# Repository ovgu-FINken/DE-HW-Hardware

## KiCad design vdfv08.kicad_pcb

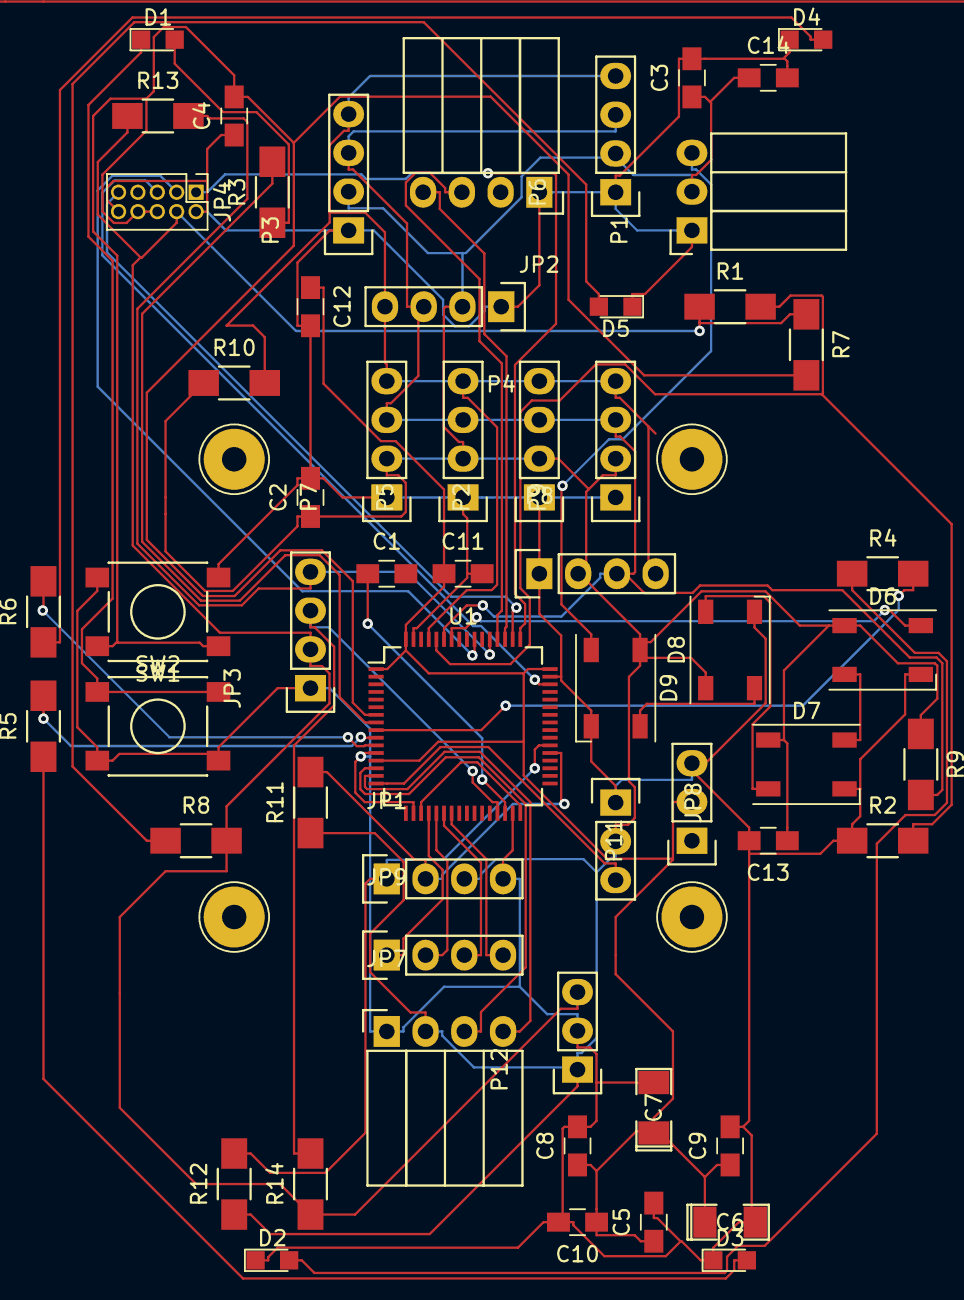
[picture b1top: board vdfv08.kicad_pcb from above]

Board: 2 copper layers, 58 parts (0 on the bottom side), 42 nets.

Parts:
C1: 2.2nF; C_0805_HandSoldering
C2, C3, C8, C9, C10, C11, C12, C13, C14: 0.1U; C_0805_HandSoldering
C4, C5: 10nF; C_0805_HandSoldering
C6: 1U; SMD-1206_Pol
C7: 4.7U; SMD-1206_Pol
D1, D2, D3, D4, D5: LED; LED_0805
D6, D7, D8, D9: WS2812B; LED_WS2812B-PLCC4
JP1: OPTICAL-FLOW; Socket_Strip_Straight_1x04
JP2: AUTOPILOT; Socket_Strip_Angled_1x04
JP3: ILLUMINSENSORI2C2; Socket_Strip_Straight_1x04
JP4: JTAG; Pin_Header_Straight_2x05_Pitch1.27mm
JP7: IR DISTANCE; Socket_Strip_Angled_1x04
JP8: CURENT SENSOR; Socket_Strip_Straight_1x03
JP9: RANGING SENSOR; Socket_Strip_Straight_1x04
P1: CONN WS2812; Socket_Strip_Angled_1x03
P2, P3, P4, P5, P6, P7, P8, P9: I2C-SONAR; Socket_Strip_Straight_1x04
P11: voltage conn; Socket_Strip_Straight_1x03
P12: voltage connector; Socket_Strip_Straight_1x03
R1, R2, R9, R10, R11, R12, R13, R14: 4.7KE; R_1206_HandSoldering
R3, R4, R5, R6, R8: 470E; R_1206_HandSoldering
R7: 10KE; R_1206_HandSoldering
SW1, SW2: SW_PUSH; SW_SPST_PTS645
U1: STM32F446RETx; LQFP-64_10x10mm_Pitch0.5mm

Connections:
/3.3V: JP3.2, JP4.4, P12.3, R1.1, R7.1, R8.2, R13.1, R14.1
/5V: C2.1, C3.1, C13.1, C14.1, D6.1, D7.1, D8.1, D9.1, JP1.3, JP7.2, JP8.2, P1.2, P2.2, P3.2, P4.2, P5.2, P6.2, P7.2, P8.2, P9.2, P12.1, R9.1, R10.1, R11.1, R12.1
/BOOT0: R1.2, R2.2, U1.60
/DIN: D6.4, U1.58
/DIN1: D6.2, D7.4
/DIN2: D7.2, D8.4
/DIN3: D8.2, D9.4
/ENABLE: JP7.4, U1.15
/I2C2SCL: JP3.3, R14.2, U1.29
/I2C2SDA: JP3.4, R13.2, U1.53
/NRST: C4.2, JP4.6, JP4.8, R7.2, SW1.1, U1.7
/OUT: JP7.3, U1.14
/PC0: R3.2, U1.8
/PC1: R4.2, U1.9
/PC2: R5.2, U1.10
/PC3: R6.2, U1.11
/PC10: JP2.4, U1.51
/PC11: JP2.3, U1.52
/SCL: P2.4, P3.4, P4.4, P5.4, P6.4, P7.4, P8.4, P9.4, R10.2, U1.61
/SDA: P2.3, P3.3, P4.3, P5.3, P6.3, P7.3, P8.3, P9.3, R9.2, U1.59
/SDI: JP4.9, U1.50
/SWCLK: JP4.1, U1.49
/SWDIO: JP4.5, U1.46
/SWO: JP4.3, U1.55
GND: C2.2, C3.2, C4.1, C5.2, C6.2, C7.2, C8.2, C9.2, C10.2, C11.2, C12.2, C13.2, C14.2, D2.1, D3.1, D4.1, D5.1, D6.3, D7.3, D8.3, D9.3, JP1.4, JP2.1, JP3.1, JP4.2, JP4.10, JP7.1, JP8.1, P1.1, P2.1, P3.1, P4.1, P5.1, P6.1, P7.1, P8.1, P9.1, P11.3, P12.2, R2.1, SW1.2, SW2.2, U1.12, U1.18, U1.31, U1.47, U1.63
unnamed: C1.1, U1.30
unnamed: C5.1, C6.1, C7.1, C8.1, C9.1, C10.1, C11.1, C12.1, P11.2, U1.1, U1.13, U1.48, U1.64
unnamed: D1.1, SW2.1
unnamed: D1.2, R3.1
unnamed: D2.2, R4.1
unnamed: D3.2, R5.1
unnamed: D4.2, R6.1
unnamed: D5.2, R8.1
unnamed: D9.2, P1.3
unnamed: JP1.1, R12.2, U1.38
unnamed: JP1.2, R11.2, U1.37
unnamed: JP8.3, U1.16
unnamed: JP9.1, U1.20
unnamed: JP9.2, U1.21
unnamed: JP9.3, U1.22
unnamed: JP9.4, U1.23
unnamed: U1.19, U1.32
